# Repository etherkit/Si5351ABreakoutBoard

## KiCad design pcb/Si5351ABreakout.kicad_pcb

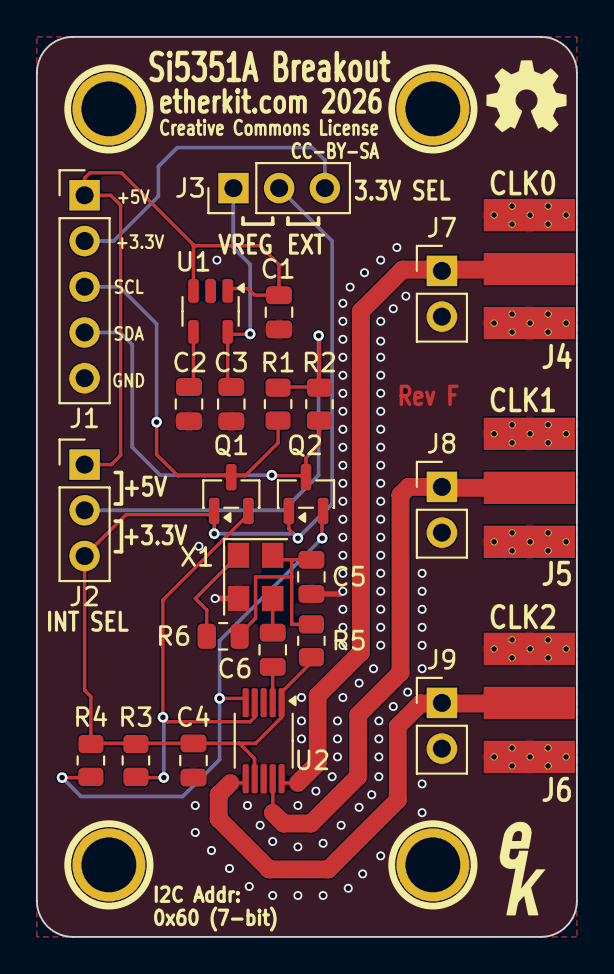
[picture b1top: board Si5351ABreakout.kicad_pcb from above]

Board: 2 copper layers, 30.0 x 50.0 mm, 31 parts (0 on the bottom side), 18 nets.

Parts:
1PIN, 1PIN#2, 1PIN#3, 1PIN#4: P***; MOUNTINGHOLE
C1: 1u MLCC; C_0805_2012Metric
C2, C4, C5, C6: 100n; C_0805_2012Metric
C3: 4.7u MLCC; C_0805_2012Metric
J1: Power/Data; Pin_Header_Straight_1x05_Pitch2.54mm
J2: PS SEL; Pin_Header_Straight_1x03_Pitch2.54mm
J3: 3.3V SEL; Pin_Header_Straight_1x03_Pitch2.54mm
J4, J5, J6: SMA-F; SMA-ENDLAUNCH
J7: CLK0; Pin_Header_Straight_1x02_Pitch2.54mm
J8: CLK1; Pin_Header_Straight_1x02_Pitch2.54mm
J9: CLK2; Pin_Header_Straight_1x02_Pitch2.54mm
Q1, Q2: BSS138; SOT-23
R1, R2, R3, R4: 10k; R_0805_2012Metric
R5: 10R; R_0805_2012Metric
R6: 0R; R_0805_2012Metric
Ref**: Val**; EtherkitLogoSmall
U1: LP2985-3.3; SOT-23-5
U2: Si5351A-B; MSOP-10_3x3mm_P0.5mm
X1: 25MHz TCXO; Oscillator_SMD_SeikoEpson_SG8002CE-4Pin_3.2x2.5mm

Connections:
+3.3V: J1.2, J3.3
+3.3VREG: C4.1, J2.3, J3.2 (PM), Q1.1, Q2.1, R3.1, R4.1, R5.1, U2.1 (VDD), U2.7 (VDDO)
+5V: C1.1, J1.1, J2.1, U1.1 (VIN), U1.3 (ON)
GND: 1PIN.1, 1PIN#2.1, 1PIN#3.1, 1PIN#4.1, C1.2, C2.2, C3.2, C4.2, C5.2, J1.5, J4.2 (Ext), J5.2 (Ext), J6.2 (Ext), J7.2 (PM), J8.2 (PM), J9.2 (PM), U1.2 (GND), U2.8 (GND), X1.2 (GND)
unnamed: J2.2 (PM), R1.1, R2.1
unnamed: C3.1, J3.1, U1.5 (VOUT)
unnamed: J4.1 (In), J7.1, U2.10 (CLK0)
unnamed: J5.1 (In), J8.1, U2.9 (CLK1)
unnamed: J6.1 (In), J9.1, U2.6 (CLK2)
unnamed: J1.3, Q1.3, R1.2
unnamed: Q1.2, R3.2, U2.4 (SCL)
unnamed: J1.4, Q2.3, R2.2
unnamed: Q2.2, R4.2, U2.5 (SDA)
unnamed: C2.1, U1.4 (BP)
unnamed: C6.2, U2.2 (XA)
unnamed: R6.2, X1.1 (OE)
unnamed: C6.1, X1.3 (OUT)
unnamed: C5.1, R5.2, R6.1, X1.4 (VDD)

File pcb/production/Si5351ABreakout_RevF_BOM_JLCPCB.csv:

"Comment","Designator","Footprint","LCSC Part #"
"1u MLCC","C1","Capacitor_SMD:C_0805_2012Metric","C28323"
"100n","C2,C4-C6","Capacitor_SMD:C_0805_2012Metric","C49678"
"4.7u MLCC","C3","Capacitor_SMD:C_0805_2012Metric","C1779"
"BSS138","Q1,Q2","Package_TO_SOT_SMD:SOT-23","C40912"
"10k","R1-R4","Resistor_SMD:R_0805_2012Metric","C17414"
"10R","R5","Resistor_SMD:R_0805_2012Metric","C17415"
"LP2985-3.3","U1","Package_TO_SOT_SMD:SOT-23-5","C16085"
"Si5351A-B","U2","Package_SO:MSOP-10_3x3mm_P0.5mm","C504891"
"25MHz TCXO","X1","Oscillator:Oscillator_SMD_SeikoEpson_SG8002CE-4Pin_3.2x2.5mm","C48888230"

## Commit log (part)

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2014-07-07 Schematic fix
2014-08-07 Rev B - I2C level conv, voltage regulator
2015-01-18 Rev C updates
2015-02-16 Update schematic, PCB 50 ohm output traces
2015-10-04 Add mechanical drawing
2016-04-11 Update BOM for new TCXO
2017-01-29 Rev D PCB changes
2017-07-16 Update documentation
2017-07-16 Documentation update for Rev C
2017-07-16 Rev D Update
2017-07-17 Fix Rev mixup
2021-03-24 Update BOM to indicate new TCXO

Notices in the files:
pcb/Si5351ABreakout.kicad_pcb:
Creative Commons License CC-BY-SA
CC-BY-SA
